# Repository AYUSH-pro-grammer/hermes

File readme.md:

# Hermes Motion Meter

For my Hermes project, I made a compact handheld motion detector based on the MPU6050 IMU, a XIAO RP2040 microcontroller, and a 0.96" OLED screen. The board reads acceleration and rotational values of the sensor and outputs it on the screen.

I decided to use the MPU6050 because I wanted to know more about IMUs and how to make a device which detects motion. Also, since the MPU6050 communicates using I²C protocol, it helped me understand such concepts as pull-up resistors, datasheets, decoupling capacitors, and PCB designing.

## Schematic

The circuit board is controlled by the XIAO RP2040. Both the MPU6050 and the OLED display are connected through the I²C bus, meaning that they use common SDA and SCL pins.

### Connections

* XIAO RP2040
* MPU6050 IMU
* 0.96" I²C OLED Display

The MPU6050 is connected as follows:

* VDD → 3.3V
* VLOGIC → 3.3V
* GND → GND
* SDA → SDA
* SCL → SCL
* AD0 → GND
* INT → GPIO D6

The OLED screen is connected to the same I²C bus:

* VCC → 3.3V
* GND → GND
* SDA → SDA
* SCL → SCL

Two 4.7kΩ pull-up resistors were used for the SDA and SCL pins in order to follow the I²C specification.

Also, the MPU6050 employs decoupling capacitors in order to stabilize the voltage and minimize noise.

## PCB Design

The board was created in KiCad.

As MPU6050 is a tiny QFN device, I spent much time making sure that everything in the datasheet and footprint was checked properly. Routing the board was quite easy due to the fact that most of the connections were only four pins:

* SDA
* SCL
* 3V3
* GND

OLED and XIAO RP2040 are connected via headers, whereas MPU6050 and passives were soldered to the PCB.

Additionally, I have added silkscreen labels in order to simplify the assembly process.

# Bill of Materials (BOM)

| Part                             | Function                                                                    | Quantity | Supplier     |
| -------------------------------- | --------------------------------------------------------------------------- | -------- | ------------ |
| Seeed XIAO RP2040                | Main microcontroller for processing sensor data and controlling the display | 1        | Seeed Studio |
| MPU6050                          | 3-axis accelerometer and 3-axis gyroscope sensor for motion detection       | 1        | Robu.in      |
| 0.96" OLED Display (SSD1306 I²C) | Displays real-time acceleration and rotation data                           | 1        | Robu.in      |
| 4.7kΩ Resistor                   | I²C SDA pull-up resistor                                                    | 1        | Generic      |
| 4.7kΩ Resistor                   | I²C SCL pull-up resistor                                                    | 1        | Generic      |
| 0.1µF Capacitor                  | Decoupling capacitor for MPU6050 power stabilization                        | 2        | Generic      |
| 1µF Capacitor                    | Power filtering capacitor                                                   | 1        | Generic      |
| Custom PCB                       | Main circuit board for all components                                       | 1        | LionCircuits |

## Purchase Links

| Component                        | Purchase Link                                                                                                                                                       |
| -------------------------------- | ------------------------------------------------------------------------------------------------------------------------------------------------------------------- |
| Seeed XIAO RP2040                | [Seeed Studio Product Page](https://www.seeedstudio.com/XIAO-RP2040-v1-0-p-5026.html)                                                        |
| Seeed XIAO RP2040 (India)        | [Robu.in Product Page](https://robu.in/product/seeed-studio-xiao-rp2040-v1-0/)                                                               |
| MPU6050 Sensor Module            | [Robu.in MPU6050 Module](https://robu.in/product/mpu-6050-gyro-sensor-2-accelerometer/)                                                      |
| MPU6050 IC                       | [Robu.in MPU6050 IC](https://robu.in/product/mpu-6050-qfn-24-3-axis-gyro-accelerometer-ic/)                                                  |
| 0.96" OLED Display (SSD1306 I²C) | [Robu.in OLED Display (Blue)](https://robu.in/product/0-96-inch-i2c-iic-oled-lcd-module-4pin-with-vcc-gnd-blue/)                             |
| 0.96" OLED Display (SSD1306 I²C) | [Robu.in OLED Display (White)](https://robu.in/product/0-96-inch-i2c-iic-oled-lcd-module-4pin-with-vcc-gnd-white/)                           |
| 0.96" OLED Display (SSD1306 I²C) | [Robu.in OLED Display (128×64 SSD1306)](https://robu.in/product/0-96-inch-128x64-ssd1306-iic-interface-4-pin-oled-module-blue-color-screen/) |
| 4.7kΩ Resistor                   | [Robu.in Resistors Collection](https://robu.in/product-category/passive-components/resistors/)                                               |
| 0.1µF Ceramic Capacitor          | [Robu.in Capacitors Collection](https://robu.in/product-category/passive-components/capacitors/)                                             |
| 1µF Capacitor                    | [Robu.in Capacitors Collection](https://robu.in/product-category/passive-components/capacitors/)                                             |
| PCB Manufacturing                | [LionCircuits](https://lioncircuits.com/)                                                                                                    |

## Component Summary

The Hermes Motion Meter is built around the Seeed XIAO RP2040 microcontroller. Motion sensing is provided by the MPU6050 IMU, which combines a 3-axis accelerometer and a 3-axis gyroscope. A 0.96-inch SSD1306 OLED display connected through the I²C bus is used to display sensor readings in real time.

The I²C communication lines (SDA and SCL) use 4.7kΩ pull-up resistors. Two 0.1µF decoupling capacitors and one 1µF filtering capacitor are included to ensure stable operation of the MPU6050 and reduce power supply noise. All components are mounted on a custom-designed PCB manufactured through LionCircuits.

## Assembly

Upon receiving the PCB and components, I proceeded to assemble the circuit.

The MPU6050 module was the hardest part due to its tiny size; I applied flux and soldered each pin making sure there were no solder bridges. After the MPU6050 module had been soldered, all other components were much easier to solder.

Then I soldered passive components, and after that the OLED header and the XIAO RP2040 headers.

After assembling the board, I flashed the firmware and tested whether the sensor was working using I²C.

## Firmware

Firmware is used to initialize MPU6050 and OLED via the I²C bus.

Display shows:

* X axis, Y axis, and Z axis acceleration 
* X axis, Y axis, and Z axis rotation rate
* Real-time motion of the device

XIAO RP2040 is always reading data from MPU6050 and updating OLED display.

## What I Learned

From this project, I learned about:

* Datasheets reading
* Schematics designing
* PCB routing
* I²C protocol
* Pull-up resistors
* Decoupling capacitors
* Surface mount soldering
* Motion sensors usage

Overall, Hermes was an enjoyable project that provided a lot of valuable experience in developing a custom-made sensor board.

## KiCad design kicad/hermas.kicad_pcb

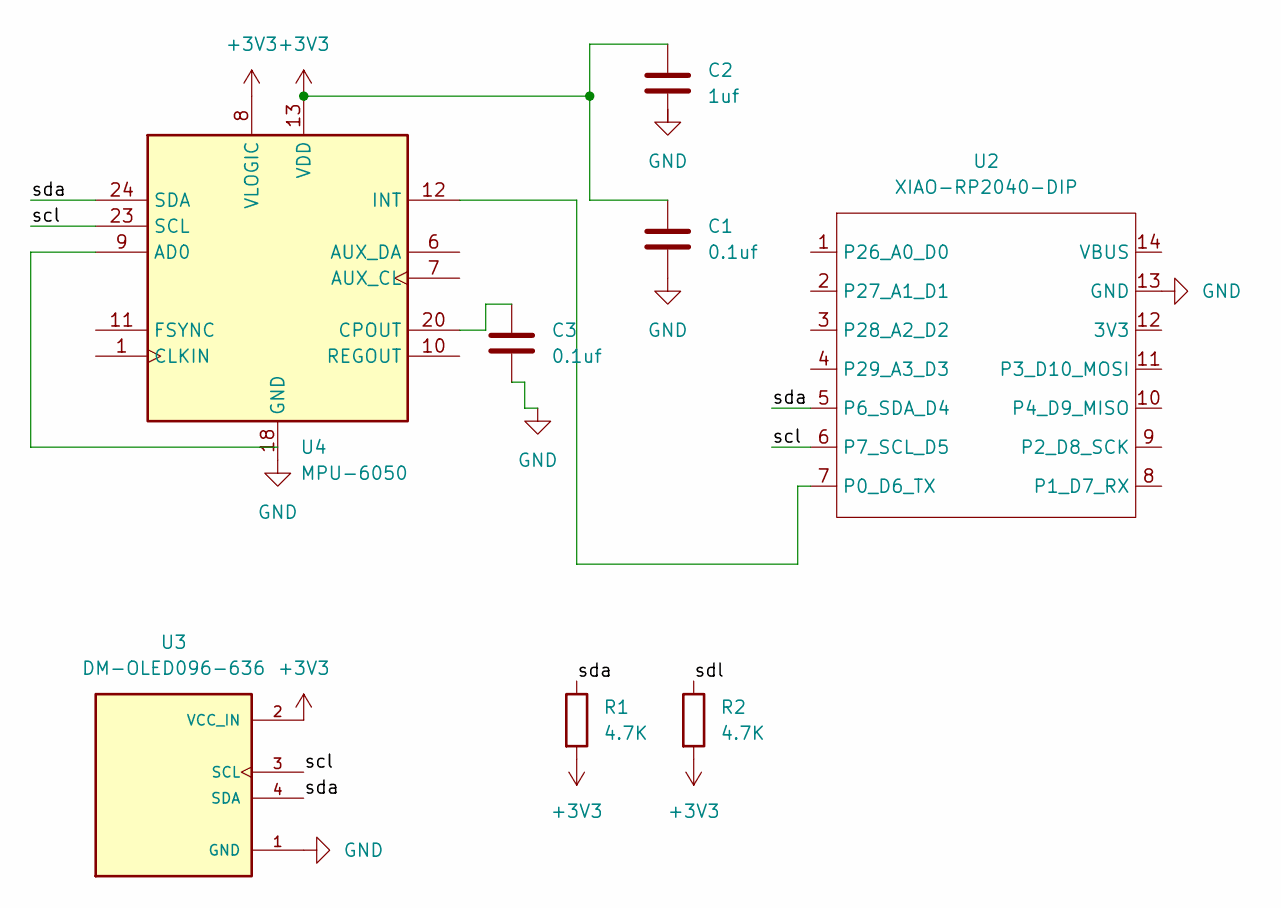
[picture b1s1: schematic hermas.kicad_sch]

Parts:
C1, C3: 0.1uf; C_Disc_D3.0mm_W1.6mm_P2.50mm
C2: 1uf; C_Disc_D3.0mm_W1.6mm_P2.50mm
R1, R2: 4.7K; R_Axial_DIN0207_L6.3mm_D2.5mm_P7.62mm_Horizontal
U2: XIAO-RP2040-DIP
U3: DM-OLED096-636; MODULE_DM-OLED096-636; PARTREV 2018-09-10
U4: MPU-6050; InvenSense_QFN-24_4x4mm_P0.5mm

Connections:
+3V3: C1.1, C2.1, R1.2, R2.2, U3.2 (VCC_IN), U4.8 (VLOGIC), U4.13 (VDD)
/scl: U2.6 (P7_SCL_D5), U3.3 (SCL), U4.23 (SCL)
/sda: R1.1, U2.5 (P6_SDA_D4), U3.4 (SDA), U4.24 (SDA)
/sdl: R2.1
GND: C1.2, C3.2, U2.13 (GND), U3.1 (GND), U4.18 (GND)
unnamed: U2.7 (P0_D6_TX), U4.12 (INT)
unnamed: C3.1, U4.20 (CPOUT)

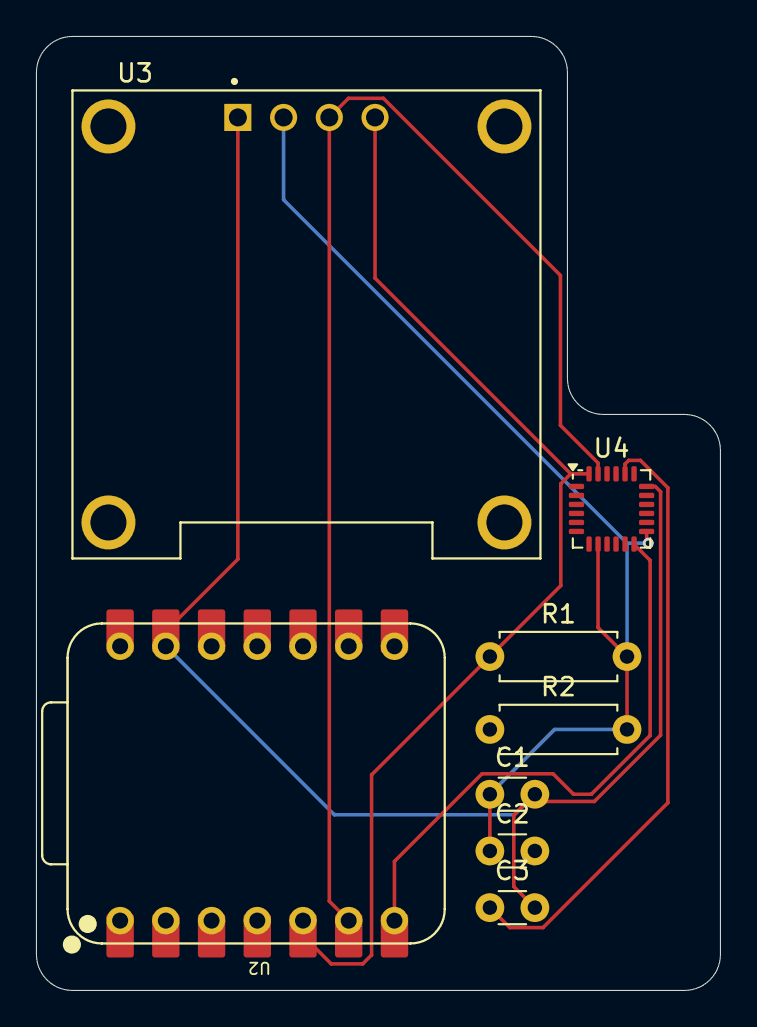
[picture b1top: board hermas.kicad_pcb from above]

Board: 2 copper layers, 38.0 x 53.0 mm, 8 parts (0 on the bottom side), 6 nets.

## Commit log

2026-06-20 added all
2026-06-20 Update Bill of Materials and add purchase links
